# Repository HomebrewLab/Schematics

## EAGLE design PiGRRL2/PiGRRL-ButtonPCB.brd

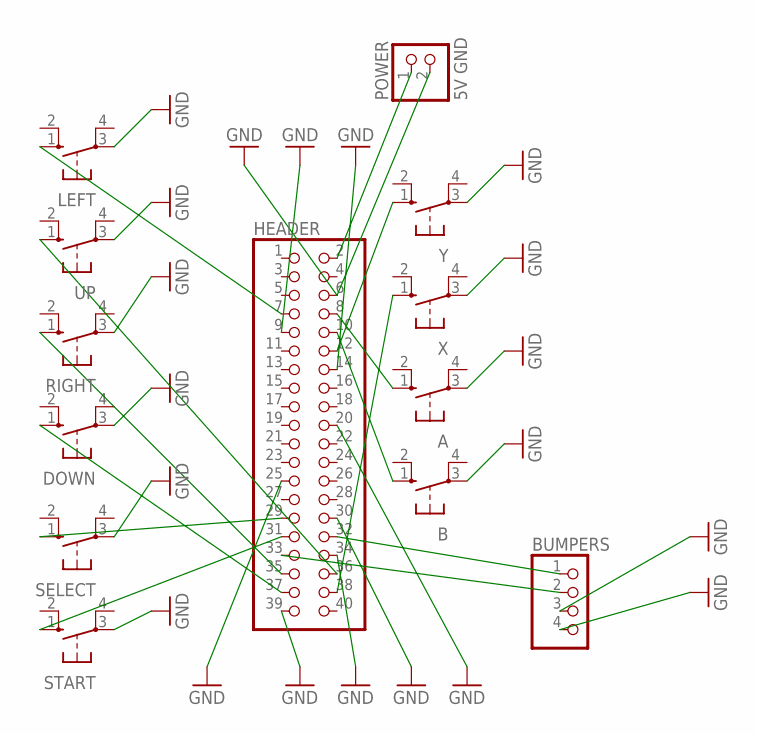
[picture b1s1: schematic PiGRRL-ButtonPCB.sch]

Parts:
A: 10-XX; B3F-10XX
B: 10-XX; B3F-10XX
BUMPERS: PINHD-1X4; 1X04
DOWN: 10-XX; B3F-10XX
HEADER: PINHD-2X20; 2X20
LEFT: 10-XX; B3F-10XX
POWER: 5V GND; 1X02
RIGHT: 10-XX; B3F-10XX
SELECT: 10-XX; B3F-10XX
START: 10-XX; B3F-10XX
UP: 10-XX; B3F-10XX
X: 10-XX; B3F-10XX
Y: 10-XX; B3F-10XX

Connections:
GND: A.3, B.3, BUMPERS.3, BUMPERS.4, DOWN.3, HEADER.6, HEADER.9, HEADER.14, HEADER.20, HEADER.25, HEADER.30, HEADER.34, HEADER.39, LEFT.3, POWER.2, RIGHT.3, SELECT.3, START.3, UP.3, X.3, Y.3
unnamed: HEADER.7, LEFT.1 (S)
unnamed: HEADER.36, UP.1 (S)
unnamed: HEADER.12, Y.1 (S)
unnamed: HEADER.35, RIGHT.1 (S)
unnamed: DOWN.1 (S), HEADER.37
unnamed: HEADER.38, X.1 (S)
unnamed: A.1 (S), HEADER.8
unnamed: B.1 (S), HEADER.10
unnamed: HEADER.29, SELECT.1 (S)
unnamed: HEADER.31, START.1 (S)
unnamed: HEADER.2, POWER.1
unnamed: BUMPERS.1, HEADER.32
unnamed: BUMPERS.2, HEADER.33

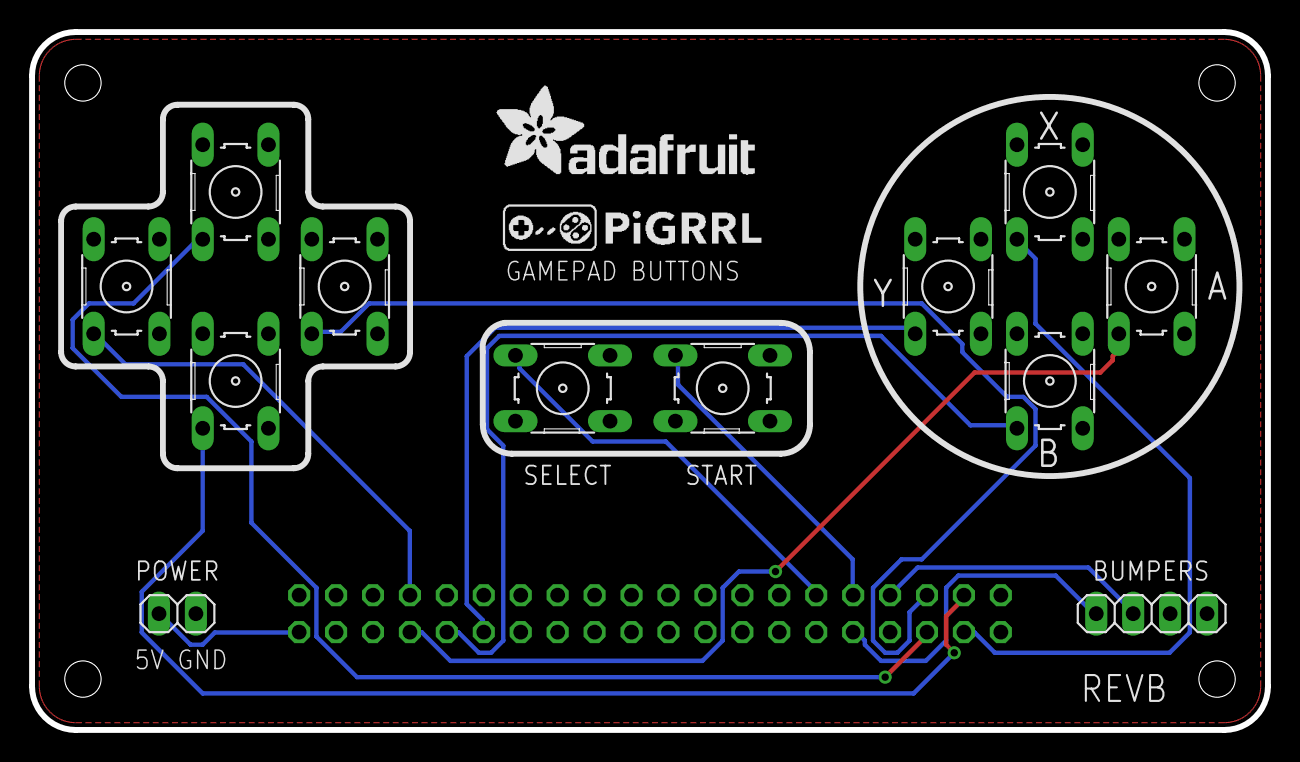
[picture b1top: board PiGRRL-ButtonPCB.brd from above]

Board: 2 copper layers, 85.0 x 48.0 mm, 13 parts (1 on the bottom side), 14 nets.

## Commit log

2025-02-03 init repo
2025-02-20 ignore usless file
2025-02-20 update pigrrl
2025-02-20 Controller Casing Schematics
2025-02-21 controller casing rev3
2025-02-21 SwiftIOSchematic
2025-02-21 cc rev 4
2025-02-21 new button for rev4
2025-02-22 Create shit
